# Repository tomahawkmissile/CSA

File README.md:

# CSA

This program was for my final project for my high school computer science class. It is very basic and it is non-modular. It takes in an EAGLE board XML file and is able to produce a couple of metrics about it. These metrics include listing all capacitors, getting the total length of all copper traces of a certain signal, and getting the total area of all copper polygons of a certain signal.

Usage: java -jar XML.jar <file> [args]

Arguments Available:
# demo                =   run demonstration program
# listCapacitors      =   list capacitors in EAGLE XML document
# getLength <signal>  =   get total signal length of a given signal name
# getArea <signal>    =   get total signal polygon area given a signal name

**Note: output may be very large, and you will have the option to save it to a text file.**

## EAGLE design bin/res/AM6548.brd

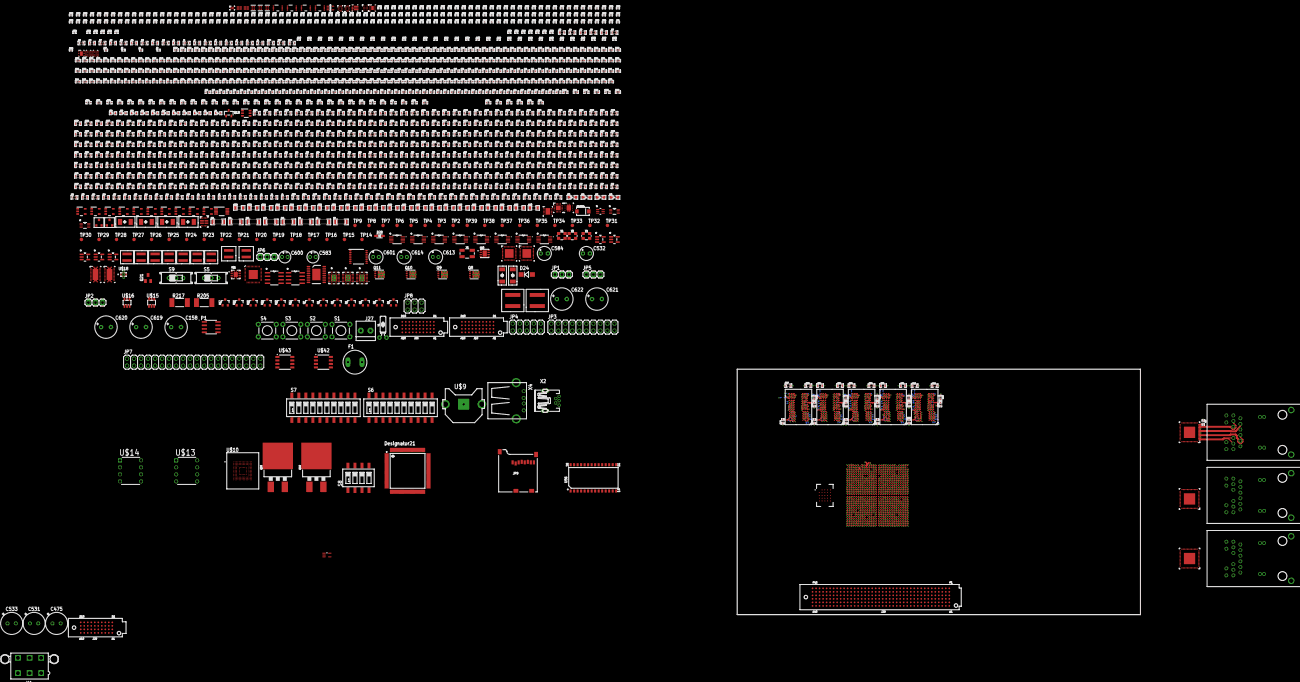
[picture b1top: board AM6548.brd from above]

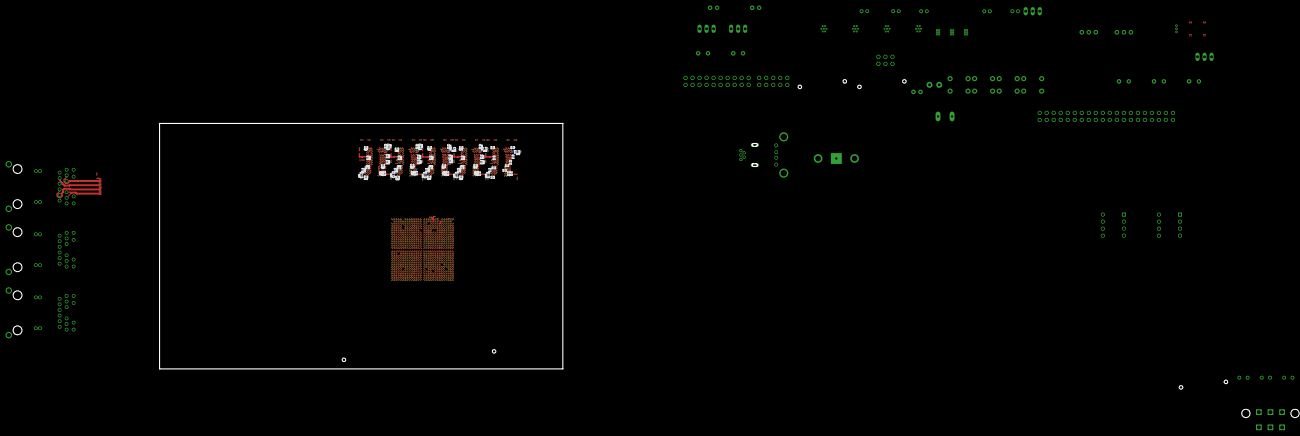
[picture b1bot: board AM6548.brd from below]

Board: 12 copper layers, 1462 parts (66 on the bottom side), 1005 nets.

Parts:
C1, C2, C3, C4, C5, C6, C7, C8, C9, C10, C11, C12, C13, C14, C15, C16, C17, C18, C19, C20, C21, C22, C23, C24, C26, C27, C28, C29, C52, C91, C92, C93, C94, C95, C96, C152, C153, C182, C184, C185, C192, C195, C206, C207, C426, C427, C447, C448, C449, C450, C451, C452, C453, C454, C455, C456, C457, C465, C466, C467, C474, C501, C502, C521, C525, C526, C527, C530, C568, C570, C576, C581, C591, C593, C595, C596: 0.1uF; 0603
C25, C30, C155, C165, C173, C178, C186, C201, C211, C212, C520, C522: 0.01uF; 0603
C31, C47, C166, C168, C204: 2.2uF; 0603
C32, C151, C179, C180, C191, C468, C569, C571, C592, C594, C602, C603: 1uF; 0603
C33: 15pF; 0603
C34, C78, C87, C90, C175, C181, C203, C205, C209, C484, C491, C496, C507, C514, C519, C529: 10uF; 0603
C35, C40, C41, C42, C43, C65, C66, C67, C69, C341, C343, C344, C358, C360, C361, C375, C377, C378, C392, C394, C395, C409, C411, C412, C523, C524, C575: 0.01uF; 0402
C36, C38, C39, C45, C48, C51, C53, C54, C55, C56, C57, C58, C59, C60, C61, C62, C63, C64, C70, C71, C72, C73, C79, C80, C81, C82, C85, C98, C342, C359, C376, C393, C410, C476, C477, C478, C479, C485, C486, C487, C492, C493, C497, C498, C499, C500, C508, C509, C510, C515, C516, C572, C574, C578, C579, C587, C588, C589, C590, C597: 0.1uF; 0402
C37, C44, C46, C74, C75, C76, C77, C83, C84, C86, C88, C89, C480, C481, C482, C483, C488, C489, C490, C494, C495, C503, C504, C505, C506, C511, C512, C513, C517, C518, C609, C632, C633: 1uF; 0402
C49, C50: 18pF; 0603
C68, C97: 8.2pF; 0402
C99, C111, C112, C113, C114, C115: 2.2uF; 0201
C100, C101, C102, C103, C104, C105, C106, C107, C108, C109, C110, C118, C119, C120, C121, C132, C133, C134, C135, C146, C147, C160, C218, C226, C227, C233, C234, C243, C244, C252, C253, C254, C255, C269, C289, C290, C303, C340: 1uF; 0201
C116, C117, C130, C131, C144, C145, C231, C232, C241, C242, C250, C251: 10uF; 0201
C122, C123, C124, C125, C126, C127, C128, C129, C136, C137, C138, C139, C140, C141, C142, C143, C219, C220, C221, C222, C223, C224, C225, C228, C229, C230, C235, C236, C237, C238, C239, C240, C245, C246, C247, C248, C249, C256, C257, C258, C259, C260, C261, C262, C263, C264, C265, C266, C267, C268, C270, C271, C272, C273, C274, C275, C276, C277, C278, C279, C280, C281, C282, C283, C284, C285, C286, C287, C288, C291, C293, C294, C295, C296, C297, C298, C299, C300, C304, C305, C307, C308, C309, C310, C311, C312, C313, C314, C315, C316, C317, C319, C320, C321, C322, C323, C324, C325, C326, C327, C328, C329, C330, C332, C334, C335, C336, C337, C338, C339, C430, C431, C432, C433, C434, C435, C436, C437, C438, C439, C440, C441, C442, C443, C444, C445: 0.1uF; 0201
C148, C149, C464, C469, C470, C472, C528: 4.7uF; 0603
C150: 0.47uF; 0805
C154, C172, C606: 100pF; 0603
C156, C171: 0.056uF; 0603
C157, C161, C174, C187, C188, C189, C190, C615, C616: 47uF; 0805
C158: 220uF; E3,5-8
C159: 100uF; 0805
C162, C193, C586: 10uF; 0805
C163: 1uF; 0805
C164, C194, C582: 0.1uF; 0805
C167, C608, C617, C618: 0.47uF; 0603
C169, C170: 33pF; 0603
C176, C177, C183, C198, C199, C446, C611, C623: 22uF; 0603
C196: 0.015uF; 0603
C197: 150pF; 0603
C200: 200pF; 0603
C202, C210, C213, C214, C345, C350, C362, C367, C379, C384, C396, C401, C413, C418: 22uF_6.3V; 0603
C208, C471, C473: 0.22uF; 0603
C215, C216, C217, C580: DNI; 0603
C292, C301, C302, C306, C318, C331, C333, C346, C347, C348, C349, C351, C352, C353, C354, C355, C356, C357, C363, C364, C365, C366, C368, C369, C370, C371, C372, C373, C374, C380, C381, C382, C383, C385, C386, C387, C388, C389, C390, C391, C397, C398, C399, C400, C402, C403, C404, C405, C406, C407, C408, C414, C415, C416, C417, C419, C420, C421, C422, C423, C424, C425, C428, C429, C610, C628, C629, C630, C631: 0.01uF; 0201
C458, C459: 12.5pF; 0402
C460, C461, C462, C463, C566, C567: TBD; 0402
C475, C531: 470uF; CAPPRD300W65D800H1200B
C532: 100uF_10V; E2,5-5
C533: 680uF; CAPPRD300W65D800H1200B
C577: DNI; 0402
C583: 22uF_100V; E2-4
C584: 100uF_63V; E2,5-5
C585: 22uF; 0805
C598: 4.7uF; 0402
C599, C624, C625, C626: 1000pF; 0603
C600: 2.2uF; E2-4
C601: 10uF; E2-5
C604: 0.047uF; 0603
C605: 220pF; 0603
C607: 820pF; 0603
C612, C627: DNI; 0201
C613: 100uF; E2-5
C614: 220uF; E2-5
C619, C622: 270uF; E3,5-8
C620, C621: 470uF; E3,5-8
C634, C635: 22uF; 0402
D1: Blue; 0603.LED
D2: Purple; 0603.LED
D3, D4, D7, D23: TPD1E10B06DPYT; DFN100X60X45-2N
D5, D6: Green; 0603.LED
D8, D19, D20, D21, D22, D31: White; 0603.LED
D24: SUM60N10; DO214BA
D25: Orange; 0603.LED
D26, D29: Red; 0805.LED
D27: Blue; 0805.LED
D28: BZT52C13S; SOD-323
D30: Green; 0805.LED
F1: 10A; TR5
FL1, FL2, FL4, FL5, FL6, FL7, FL8, FL9, FL10, FL11, FL12, FL13, FL14, FL15, FL16, FL17, FL18, FL19: 120R; 0402
FL3: 240R; 0402
FL20, FL21: 26R; 0402
FL22: 120R; 0603
FL26, FL27, FL28: 0603
FL50: DNI; 0402
FL51: 120E; 0402
J1, J2, J3, J4, J5, J6, J7, J8, J9, J11, J12, J13, J14, J15, J16, J17, J18, J19, J20, J21, J22, J23, J24, J25: 0603
J10, J26, J29: SEAF-10-XX.X-XX-04-X-A
J27: 1X2-3.5MM
J28: SEAF-40-XX.X-XX-06-X-A
JP1: PORZ_BYP; 1X03
JP2, JP5: I2C_COMBINE; 1X03
JP3: JTAG-20-ARM; 2X10
JP4: JTAG-10-TM4C; 2X05
JP6: 1X03
JP7: AUTOMATOR; 2X20
JP8: 2X03
JP9: USD-SDIO-SOCKET; MICRO-SD-SOCKET-SDIO
P1: SOIC127P600X175-8N
Q1, Q2, Q3, Q4, Q5, Q6, Q7, Q12, Q13, Q14, Q15, Q16, Q17: 220mA/50V/3.5Ω; SOT23-3
Q8, Q9, Q10, Q11: CSD18543Q3A; SON65P300X315X90-9N
Q18: SOT23-R
Q19, Q20: 100A/100V/6.8mΩ; TO-263/D2PAK
Q21: BSS138; SOT23
R1, R2, R4, R5, R7, R8, R10, R11, R13, R14, R16, R17, R19, R20, R22, R23: 10_1%; 0603
R3, R9, R12: 0.002_1%; 1206
R6, R15, R18, R21, R24: 0.01_0.5%; 1206
R25, R26, R28, R29, R30, R31, R32, R33, R34, R35, R36, R37, R38, R39, R40, R123, R124, R125, R126, R152, R208, R230, R237, R243, R256, R257, R258, R551, R553, R617: 100k; 0603
R27, R328, R342: 11k_1%; 0402
R41: 2.2k; 0603
R42, R43, R44, R45, R46, R47, R48, R49, R50, R51, R52, R53, R330, R331, R332, R333, R334, R335, R336, R337, R338, R339, R340, R341, R344, R345, R346, R347, R348, R352, R358, R359, R360, R361, R362, R363: 22_1%; 0402
R54, R55, R58, R63, R64, R70, R89, R102, R103, R223, R225, R226, R229, R252, R262, R263, R264, R282, R287, R288, R289, R290, R291, R292, R293, R294, R295, R296, R297, R310, R324, R325, R326, R327, R351, R364, R377, R385, R402, R403, R404, R405, R418, R461, R462, R497, R529, R532, R533, R534, R535, R539, R559, R575, R576, R578, R579, R594, R613, R614, R615, R616: 10k; 0603
R56, R57, R59, R60, R61, R62, R90, R178, R179, R241, R242, R265, R283, R284, R311, R349, R350, R365, R366, R372, R373, R374, R375, R376, R378, R379, R380, R381, R382, R383, R384, R484: DNI; 0603
R65, R66, R67, R96, R101, R206, R224, R353, R354, R355, R367, R368, R369, R524, R525, R527, R530, R550: 0R; 0603
R68, R69, R78, R219, R356, R357, R526, R528, R531: 220R; 0603
R71: 51k; 0603
R72, R93, R97, R107, R117, R149, R281, R300, R323, R388, R389, R393, R417, R494, R496, R582, R584, R585, R586, R587, R588, R589, R590, R591: 10k; 0402
R73, R98, R312, R313, R314, R315, R316, R317, R318, R319, R320, R321, R322, R501, R502, R503, R504, R505, R506, R507, R560, R561, R562, R563, R580: 22R_1%; 0402
R74, R91: 100R; 0603
R75: 330k_1%; 0603
R76: 220k_1%; 0603
R77: 180R; 0603
R79, R80, R81, R82, R170, R171, R172, R173, R174, R175, R176, R201, R244, R245, R246, R247, R248, R249, R250, R251, R253, R254, R255, R511, R512: 1k; 0402
R83, R84, R85, R86, R94, R134, R135, R136, R137, R138, R139, R140, R303, R304, R307, R386, R387, R390, R391, R392, R394, R395, R396, R397, R398, R399, R419, R420, R421, R422, R423, R424, R425, R426, R427, R428, R429, R430, R431, R432, R433, R434, R435, R436, R437, R438, R439, R440, R441, R442, R443, R444, R445, R446, R447, R448, R449, R450, R451, R452, R453, R454, R455, R456, R457, R458, R459, R460, R493, R495, R498, R508, R568, R569, R570, R571, R572, R596: DNI; 0402
R87, R99, R100, R106, R485, R486, R487, R488: 4.7k; 0402
R88: 4.87k_1%; 0402
R92: 51R; 0402
R95, R114, R177, R285, R286, R489, R490, R491, R492, R556, R592, R593: 4.7k; 0603
R104, R105, R115, R116, R133: 33R_1%; 0402
R108, R110, R111, R112, R113: 10R_1%; 0603
R109, R118, R509, R510: 100R; 0402
R119, R120, R121, R122, R153, R154, R155, R156, R157, R158, R159, R160, R161, R162, R163, R165, R166, R167, R168, R169, R259, R260, R261, R607, R618: 1k; 0603
R127, R128, R129, R130, R131, R132, R583: 100k; 0402
R141, R238: 40.2k_1%; 0603
R142, R234, R554, R601: 10k_1%; 0603
R143, R299, R301, R302, R305, R306, R308, R309, R499, R500, R543, R573, R577: 0R; 0402
R144, R145, R146, R147, R148, R150: 240R_1%; 0402
R151, R412, R413, R414, R415, R416: 330R; 0402
R164, R180, R181, R182, R184: DNI; 0201
R183: 10k; 0201
R185: 1K; 0201
R186, R187, R188, R189, R190, R191, R192, R193, R194, R195, R196, R197, R198, R199, R200, R209, R210, R266, R267, R268, R269, R270, R271, R272, R273, R274, R275, R276, R277, R278, R279, R280: 39.2R_1%; 0201
R202, R203, R204, R211, R212, R213: 10.2R; 0603
R205, R217: 0.005R; R2512
R207: 19.6k 0.1%; 0603
R214, R215, R216: 49.9R; 0603
R218: 29.4k 1%; 0603
R220: 330R; 0603
R221: 10.2k_0.1%; 0603
R222: 20.5k; 0603
R227: 60.4k; 0603
R228: 40.2k; 0603
R231: 2.05k_1%; 0603
R232: 51.1_1%; 0603
R233: 31.6k_1%; 0603
R235: 18.7_1%; 0603
R236: 8.87_1%; 0603
R239: 158k_1%; 0603
R240: 499k_1%; 0603
R298, R608, R609: 330; 0603
R329, R343, R463, R464: 2.2k; 0402
R370, R371: 220; 0603
R400, R401, R599: 22R; 0603
R406, R409: 16k_1%; 0603
R407, R410: 76.8k_1%; 0603
R408, R411: 23.2k_1%; 0603
R536: 261k_1%; 0402
R537, R538, R541, R542: 10k_1%; 0402
R540: 5.81k_1%; 0402
R544: 237k_1%; 0603
R545, R546: 47k_1%; 0603
R547: 666k_1%; 0603
R548: 5.62k_1%; 0603
R549, R555: 10k; 0805
R552: 1k; 0805
R557, R558: 3k_1%; 0402
R564, R565, R566, R567: 49.9R_1%; 0402
R574, R610, R611, R612: 1M; 0603
R581: 10R_1%; 0402
R595, R597, R598: 22R; 0402
R600: 75k_1%; 0603
R602: 18.2k_1%; 0603
R603: 0.082R_2%; 0603
R604: 1k_1%; 0603
R605: 8.66k_1%; 0603
R606: 46.4k_1%; 0603
R700, R701: 2.2k; 0201
S1, S2, S3, S4: TACTILE-PTH
S5, S9: EG1218
S6, S7: BOOTMODE; SMS-010
S8: MCU_BOOTMODE; SMS-004
SMCJ64CA: TVS; SMA-DIODE
TP2, TP3, TP4, TP5, TP6, TP7, TP8, TP9, TP14, TP15, TP16, TP17, TP18, TP19, TP20, TP21, TP22, TP23, TP24, TP25, TP26, TP27, TP28, TP29, TP30, TP31, TP32, TP33, TP34, TP35, TP36, TP37, TP38, TP39: TESTPAD_TPSQB1,27; TESTPAD_B1,27
U1: Value; ACD0784A
U2, U3, U4, U5, U6, U7, U8, U9: INA226_DGS_10; DGS10
U10: Value; RGJ0032A
U11, U12: Value; RHL0024A
U13, U21, U25: SN74AVC4T245_RGY_16; RGY16_2P55X2P05
U14, U54, U55: Value; RGZ0048B
U15, U75: Value; RSW0010A
U16, U24, U27, U46: Value; DCU0008A_N
U17, U33, U49, U50, U51, U52, U57, U58, U81, U82: Value; DBV0005A_N
U18: Value; PDT0128A_N
U19: TPD4E004_DRY_6; DRY6
U20: Value; DCK0005A_N
U22, U26: SN74AVC2T244_DQM_8; DQM8
U23, U28, U29, U30, U31: SN74LVC1G32_DBV_5; DBV5
U32: Value; PW0016A_N
U34: Value; RWG0040A
U35: Value; RLT0007A
U36, U42: Value; RWK0011B
U37: Value; DQN0004A
U38: Value; YZH0016AFAF
U39: Value; RNC0016A
U40: Value; DRV0006A
U41: Value; DRC0010J
U43: Value; DRB0008A
U44: Value; DSQ0010A
U45: Value; RGT0016C
U47, U48: SN74LVC3G17_DCU_8; DCU8
U53, U59: TPS2051B_D_8; D8
U56: INTERFACE-MCP23017-E(SOIC28); SOIC28-1.27-17.9X7.5MM
U60: TPD4S012_DRY_6; DRY6
U73: Value; RHB0032D
U76: Value; DDC0006A_N
U77: TPS3897_DRY_6; DRY6
U78: SN74LVC1G11_DCK_6; DCK6
U79: Value; DGS0010A_N
U80: MIC5060YML-TR; SON65P300X300X100-9N
U83: Value; PWP0020A_N
U$1: VSON8; SON65P300X300X100-9N
U$2: LM4040B25IDCKR13; SOT65P210X110-5N
U$3, U$4, U$5, U$6, U$7: MT40A1G8WE-083E:B
U$9: CR1220-THM
U$10: IS21ES16G; BGA153C50P14X14_1150X1300X100N
U$11, U$12, U$17: JK0-2500NL
U$13, U$14: 24LC512-E/P; DIP254P762X432-8
U$15, U$16: TMP100; SOT23-6
U$18: NFM21PC; FIL_NFM21PC105B1C3D
U$19, U$36: BZX84C2V4LT1-D; SOT-23
U$20, U$21: DB2441700L
U$22, U$25: XEL6030-152MEB
U$28, U$30, U$31, U$32: XFL4015-471MEB
U$29, U$34, U$35: XFL4020-102MEB
U$33: XEL4030-682ME_
U$38: MT35XU512ABA1G12-0SITT-PBGA-24; BGA25C100P5X5_800X600X100
U$39: XAL40XX
U$40, U$41, U$44, U$45: SSB44-E3/52T; SMB
U$42, U$43: SI4442DYSO-8; SOIC127P600X175-8
X1: 5566-6
X2: MINI-USB_SHIELD5P2-32005-601; 32005-601
X4: USB-A-H
Y1: 32.768kHz; CRYSTAL-PTH-2X6-CYL
Y2: 16MHz; CRYSTAL-SMD-5X3.2-4PAD
Y3, Y6: 25MHz; CRYSTAL-SMD-3.2X2.5MM
Y4: 24.576MHz; CRYSTAL-SMD-3.2X2.5MM

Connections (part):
!APP_RESET: J28.E1, R461.1, U33.4
!BOOTMODE_DEBUGGER_RST: JP7.21, R287.1, U10.28, U56.2
!BOOTMODE_EN: JP7.19, R262.1, R288.1, U23.1, U56.1
!DDR_RESET: R164.1, R180.2, R701.1, U1.A11, U$3.RESET_N, U$4.RESET_N, U$5.RESET_N, U$6.RESET_N, U$7.RESET_N
!EMMC_RST: R364.2, U52.4, U$10.K5
!GPIO_EMMC_RST: R326.1, U52.1, U56.21
!GPIO_MCU_RGMII_RST: R62.2, R63.1, U17.1, U56.23
!GPIO_PRG2_RGMII_RST: R350.2, R351.1, U56.22, U57.1
!JTAG_EMU_RST: JP3.15, R95.1, R111.1, U78.6
!JTAG_TRST: JP3.2, R112.1, U21.10
!LCD_BRD_TOUCH_RESET: R575.1, U56.4, U81.1
!LCD_TOUCH_RESET: J26.B9, R576.1, U81.4
!OSPI_RESET: R578.1, U82.4, U$38.A4
!OSPI_RESET_PRE: R579.1, U56.5, U82.1
!RAW_WARM_RESET: C451.2, D3.1, R295.1, S1.1, S1.2, U48.3
!RAW_WK_INT_0-13: C453.2, D4.1, R296.1, S2.1, S2.2, U48.2
!RAW_WK_INT_0-27: C454.2, D7.1, R297.1, S3.1, S3.2, U48.1
!REG_WK_INT_0-13: U48.6, U50.2
!REG_WK_INT_0-27: U48.7, U51.2
!SOC_TRST: R106.1, U1.AA3, U21.7, U25.7
!SOC_WARM_RESET: U1.F17, U49.4
!SOC_WK_INT_0-13: U1.R5, U50.4
!SOC_WK_INT_0-27: U1.P2, U51.4
!SUPERVISOR_MASTER_RESET: U47.7, U77.1
!SUPERVISOR_RAW_RESET: C576.2, D23.1, Q18.3, R539.1, S4.1, S4.2, U47.1
!TEST_LED: D8.P$2, JP7.13, R291.1
!TEST_PORZ: JP7.9, Q18.2, R293.1
!TEST_WARM_RESET: JP7.11, R292.1, U49.2
!TEST_WK_INT_0-13: JP7.15, R290.1, U50.1
!TEST_WK_INT_0-27: JP7.17, R289.1, U51.1
!TM4C_RST: JP4.10, R91.1
!WARM_RESET: U48.5, U49.1
!XDS_TRST: U18.40, U25.10
ADDR: R263.2, U10.26
BOARDID_EEPROM_A0: R373.1, R374.2, U$13.1
BOARDID_EEPROM_A1: R372.1, R375.2, U$13.2
BOARDID_EEPROM_A2: R366.1, R376.2, U$13.3
BOARDID_EEPROM_WP: R365.1, R377.2, U$13.7
BOARDID_LCD_A1: J26.B4, R577.1
BOOST_DRIVE: U83.15, U$43.4
BOOTMODE_I2C_SCL: JP7.29, R285.1, U10.29
BOOTMODE_I2C_SDA: JP7.27, R286.1, U10.30
BOOTMODE_ON: U11.22, U12.22, U13.14, U13.15, U23.4
BOOT_EEPROM_A0: R381.1, R382.2, U$14.1
BOOT_EEPROM_A1: R380.1, R383.2, U$14.2
BOOT_EEPROM_A2: R379.1, R384.2, U$14.3
BOOT_EEPROM_WP: R378.1, R385.2, U$14.7
BUCK_DRIVE: U83.19, U$42.4
CAP_VDDA_1P8_IOLDO0: C113.2, U1.AA10, U1.AA16, U1.G12, U1.G19, U1.P20
CAP_VDDA_1P8_IOLDO_WKUP: C114.2, U1.AA8, U1.V8
CAP_VDDA_1P8_SDIO: C111.2, U1.G17, U1.J17, U1.K20
CAP_VDDSHV_SDLDO: C99.2, FL20.1, U1.H18
CAP_VDD_WKUP: C115.2, C326.2, C327.2, C328.2, C329.2, U1.M22, U1.V9, U1.V11, U1.W10, U1.W12
CS: R603.1, U83.12, U$44.ANODE, U$45.ANODE
CSI0_RX0_N: J28.A3, U1.G28
CSI0_RX0_P: J28.A2, U1.F28
CSI0_RX1_N: J28.A6, U1.H27
CSI0_RX1_P: J28.A5, U1.G27
CSI0_RX2_N: J28.A8, U1.F26
CSI0_RX2_P: J28.A9, U1.G26
CSI0_RX3_N: J28.A12, U1.H25
CSI0_RX3_P: J28.A11, U1.G25
CSI0_RX4_N: J28.A15, U1.G24
CSI0_RX4_P: J28.A14, U1.F24
DDR_A0: R196.1, U1.A10, U$3.A0, U$4.A0, U$5.A0, U$6.A0, U$7.A0
DDR_A1: R197.1, U1.D9, U$3.A1, U$4.A1, U$5.A1, U$6.A1, U$7.A1
DDR_A2: R198.1, U1.C9, U$3.A2, U$4.A2, U$5.A2, U$6.A2, U$7.A2
DDR_A3: R199.1, U1.E9, U$3.A3, U$4.A3, U$5.A3, U$6.A3, U$7.A3
DDR_A4: R200.1, U1.A9, U$3.A4, U$4.A4, U$5.A4, U$6.A4, U$7.A4
DDR_A5: R209.1, U1.E8, U$3.A5, U$4.A5, U$5.A5, U$6.A5, U$7.A5
DDR_A6: R210.1, U1.F8, U$3.A6, U$4.A6, U$5.A6, U$6.A6, U$7.A6
DDR_A7: R266.1, U1.C7, U$3.A7, U$4.A7, U$5.A7, U$6.A7, U$7.A7
DDR_A8: R267.1, U1.C8, U$3.A8, U$4.A8, U$5.A8, U$6.A8, U$7.A8
DDR_A9: R268.1, U1.D7, U$3.A9, U$4.A9, U$5.A9, U$6.A9, U$7.A9
DDR_A10: R269.1, U1.E7, U$3.A10/AP, U$4.A10/AP, U$5.A10/AP, U$6.A10/AP, U$7.A10/AP
DDR_A11: R270.1, U1.A6, U$3.A11, U$4.A11, U$5.A11, U$6.A11, U$7.A11
DDR_A12: R271.1, U1.F7, U$3.A12/BC_N, U$4.A12/BC_N, U$5.A12/BC_N, U$6.A12/BC_N, U$7.A12/BC_N
DDR_A13: R272.1, U1.D6, U$3.A13, U$4.A13, U$5.A13, U$6.A13, U$7.A13
DDR_A14_WEN: R273.1, U1.C6, U$3.WE_N/A14, U$4.WE_N/A14, U$5.WE_N/A14, U$6.WE_N/A14, U$7.WE_N/A14
DDR_A15_CAS: R274.1, U1.F6, U$3.CAS_N/A15, U$4.CAS_N/A15, U$5.CAS_N/A15, U$6.CAS_N/A15, U$7.CAS_N/A15
DDR_A16_RAS: R275.1, U1.E6, U$3.RAS_N/A16, U$4.RAS_N/A16, U$5.RAS_N/A16, U$6.RAS_N/A16, U$7.RAS_N/A16
DDR_A17: R276.1, U1.E5, U$3.A17/NC, U$4.A17/NC, U$5.A17/NC, U$6.A17/NC, U$7.A17/NC
DDR_ACT_N: R280.1, U1.D8, U$3.ACT_N, U$4.ACT_N, U$5.ACT_N, U$6.ACT_N, U$7.ACT_N
DDR_ALERT_N: R183.1, U1.D5, U$3.ALERT_N, U$4.ALERT_N, U$5.ALERT_N, U$6.ALERT_N, U$7.ALERT_N
DDR_BA0: R194.1, U1.D10, U$3.BA0, U$4.BA0, U$5.BA0, U$6.BA0, U$7.BA0
DDR_BA1: R195.1, U1.E10, U$3.BA1, U$4.BA1, U$5.BA1, U$6.BA1, U$7.BA1
DDR_BG0: R278.1, U1.C10, U$3.BG0, U$4.BG0, U$5.BG0, U$6.BG0, U$7.BG0
DDR_BG1: R279.1, U1.F11, U$3.BG1, U$4.BG1, U$5.BG1, U$6.BG1, U$7.BG1
DDR_CKE: R182.2, R190.1, U1.C11, U$3.CKE, U$4.CKE, U$5.CKE, U$6.CKE, U$7.CKE
DDR_CKE1: R181.2, R191.1, U1.D12, U$3.C0/CKE1, U$4.C0/CKE1, U$5.C0/CKE1, U$6.C0/CKE1, U$7.C0/CKE1
DDR_CK_N: R187.1, U1.B8, U$3.CK_C, U$4.CK_C, U$5.CK_C, U$6.CK_C, U$7.CK_C
DDR_CK_P: R186.1, U1.A8, U$3.CK_T, U$4.CK_T, U$5.CK_T, U$6.CK_T, U$7.CK_T
DDR_CS1_N: R193.1, U1.E11, U$3.C1/CS1_N, U$4.C1/CS1_N, U$5.C1/CS1_N, U$6.C1/CS1_N, U$7.C1/CS1_N
DDR_CS_N: R192.1, U1.D11, U$3.CS_N, U$4.CS_N, U$5.CS_N, U$6.CS_N, U$7.CS_N
DDR_DM0: U1.E1, U$3.NF/DM_N/DBI_N/TDQS_I
DDR_DM1: U1.C5, U$4.NF/DM_N/DBI_N/TDQS_I
DDR_DM2: U1.D14, U$5.NF/DM_N/DBI_N/TDQS_I
DDR_DM3: U1.B17, U$6.NF/DM_N/DBI_N/TDQS_I
DDR_DM4: U1.C17, U$7.NF/DM_N/DBI_N/TDQS_I
DDR_DQ0: U1.A3, U$3.DQ6/NF
DDR_DQ1: U1.B2, U$3.DQ4/NF
DDR_DQ2: U1.C2, U$3.DQ2
DDR_DQ3: U1.D2, U$3.DQ0
DDR_DQ4: U1.E2, U$3.DQ1
DDR_DQ5: U1.G1, U$3.DQ7/NF
DDR_DQ6: U1.F2, U$3.DQ5/NF
DDR_DQ7: U1.F1, U$3.DQ3
DDR_DQ8: U1.E3, U$4.DQ6/NF
DDR_DQ9: U1.C3, U$4.DQ3
DDR_DQ10: U1.D3, U$4.DQ5/NF
DDR_DQ11: U1.B3, U$4.DQ1
DDR_DQ12: U1.D4, U$4.DQ7/NF
DDR_DQ13: U1.C4, U$4.DQ2
DDR_DQ14: U1.B4, U$4.DQ4/NF
DDR_DQ15: U1.B5, U$4.DQ0
DDR_DQ16: U1.E13, U$5.DQ1
DDR_DQ17: U1.C14, U$5.DQ6/NF
DDR_DQ18: U1.B14, U$5.DQ4/NF
DDR_DQ19: U1.A14, U$5.DQ2
DDR_DQ20: U1.E14, U$5.DQ3
DDR_DQ21: U1.B13, U$5.DQ0
DDR_DQ22: U1.C13, U$5.DQ7/NF
DDR_DQ23: U1.D13, U$5.DQ5/NF
DDR_DQ24: U1.D15, U$6.DQ3
DDR_DQ25: U1.C15, U$6.DQ5/NF
DDR_DQ26: U1.E16, U$6.DQ6/NF
DDR_DQ27: U1.E15, U$6.DQ7/NF
DDR_DQ28: U1.D16, U$6.DQ4/NF
DDR_DQ29: U1.B16, U$6.DQ1
DDR_DQ30: U1.C16, U$6.DQ0
DDR_DQ31: U1.A17, U$6.DQ2
DDR_DQ36: U1.B19, U$7.DQ0
DDR_DQ37: U1.B18, U$7.DQ1
DDR_DQ38: U1.C18, U$7.DQ2
DDR_DQ39: U1.D18, U$7.DQ4/NF
DDR_DQ40: U1.E18, U$7.DQ5/NF
DDR_DQ41: U1.E17, U$7.DQ6/NF
DDR_DQ42: U1.D17, U$7.DQ3
DDR_DQS0_N: U1.C1, U$3.DQS_C
DDR_DQS0_P: U1.D1, U$3.DQS_I
DDR_DQS1_N: U1.A4, U$4.DQS_C
DDR_DQS1_P: U1.A5, U$4.DQS_I
DDR_DQS2_N: U1.A12, U$5.DQS_C
DDR_DQS2_P: U1.A13, U$5.DQS_I
DDR_DQS3_N: U1.A16, U$6.DQS_C
DDR_DQS3_P: U1.A15, U$6.DQS_I
DDR_DQS_N: U1.A18, U$7.DQS_C
DDR_DQS_P: U1.A19, U$7.DQS_I
DDR_ODT: R188.1, U1.B11, U$3.ODT, U$4.ODT, U$5.ODT, U$6.ODT, U$7.ODT
DDR_ODT1: R189.1, U1.E12, U$3.C2/ODT1, U$4.C2/ODT1, U$5.C2/ODT1, U$6.C2/ODT1, U$7.C2/ODT1
DDR_PARITY: R277.1, U1.B10, U$3.PAR, U$4.PAR, U$5.PAR, U$6.PAR, U$7.PAR
DDR_TEN: R184.1, R185.2, U$3.TEN, U$4.TEN, U$5.TEN, U$6.TEN, U$7.TEN
DDR_VPP: C343.2, C344.2, C345.2, C360.2, C361.2, C362.2, C377.2, C378.2, C379.2, C394.2, C395.2, C396.2, C411.2, C412.2, C413.2, FL51.2, U$3.VPP@1, U$3.VPP@2, U$4.VPP@1, U$4.VPP@2, U$5.VPP@1, U$5.VPP@2, U$6.VPP@1, U$6.VPP@2, U$7.VPP@1, U$7.VPP@2
DDR_VREFCA: C208.2, C341.2, C342.2, C358.2, C359.2, C375.2, C376.2, C392.2, C393.2, C409.2, C410.2, R179.1, U44.6, U$3.VREFCA, U$4.VREFCA, U$5.VREFCA, U$6.VREFCA, U$7.VREFCA
DDR_VTT_EN: U1.P3, U75.4
DDR_VTT_EN_3V3: R237.2, U44.7, U44.9, U75.9
DIR: R264.2, R265.1, U11.2, U12.2, U13.2, U13.3
DOCK_TCK: R115.2, U32.2
ECAP0_IN_APWM0_OUT: J26.B8, U1.D21
GPIO0_16: J28.B4, U1.R28
GPIO0_20: J28.B6, U1.T28
GPIO0_21: J28.A39, R462.1, U1.P23, U33.1
GPIO0_22: J28.B9, U1.R26
GPIO0_23: J28.B7, U1.R23
GPIO0_25: J28.B8, U1.T24
GPIO0_26: J28.B5, U1.R24
GPIO0_27: J28.A38, U1.T23
GPIO1_0: J28.B10, R609.1, U1.AD18
GPIO1_1: J28.B11, R608.1, U1.AH18
GPIO1_69: J28.B12, U1.AE26
GPIO1_70: J28.B13, U1.AE28
GPIO_0-0-0: J28.D20, U1.V24
GPIO_0-0-1: J28.F28, U1.W25
GPIO_0-0-2: J28.D23, U1.W24
GPIO_0-0-3: J28.D28, U1.AA27
GPIO_0-0-4: J28.D25, U1.Y24
GPIO_0-0-5: J28.D17, U1.V28
GPIO_0-0-6: J28.D26, U1.Y25
GPIO_0-0-7: J28.D18, U1.U27
GPIO_0-0-8: J28.D19, U1.V27
GPIO_0-0-11: J28.D29, U1.AB25
GPIO_0-0-12: J28.D14, U1.AD27
GPIO_0-0-13: J28.D16, U1.AC26
GPIO_0-0-14: J28.D13, U1.AD26
GPIO_0-0-15: J28.D27, U1.AA24
GPIO_0-0-16: J28.D15, U1.AD28
GPIO_0-0-17: J28.D21, U1.U26
GPIO_0-0-18: J28.D24, U1.V25
GPIO_0-0-19: J28.D22, U1.U24
GPIO_0-1-0: J28.D40, U1.AB28
GPIO_0-1-1: J28.C39, U1.AC28
GPIO_0-1-2: J28.C37, U1.AC27
GPIO_0-1-3: J28.C38, U1.AB26
GPIO_0-1-4: J28.D37, U1.AA25
GPIO_0-1-5: J28.D38, U1.U23
GPIO_0-1-6: J28.D39, U1.AB27
GPIO_0-1-8: J28.C40, U1.W27
GPIO_0-1-11: J28.D36, U1.AB24
GPIO_0-1-12: J28.D35, U1.AC25
GPIO_0-1-13: J28.D32, U1.AD25
GPIO_0-1-14: J28.D33, U1.AD24
GPIO_0-1-15: J28.D31, U1.AE27
GPIO_0-1-16: J28.D34, U1.AC24
GPIO_1-0-0: J28.D12, U1.AE22
GPIO_1-0-1: J28.D6, U1.AG24
GPIO_1-0-2: J28.E7, U1.AF23
GPIO_1-0-3: J28.E13, U1.AD21
GPIO_1-0-4: J28.D7, U1.AG23
GPIO_1-0-5: J28.D2, U1.AF27
GPIO_1-0-6: J28.D9, U1.AF22
GPIO_1-0-7: J28.D3, U1.AG27
GPIO_1-0-8: J28.D1, U1.AF28
GPIO_1-0-11: J28.D11, U1.AF21
GPIO_1-0-12: J28.D10, U1.AH20
GPIO_1-0-13: J28.D8, U1.AH21
GPIO_1-0-14: J28.E10, U1.AG20
GPIO_1-0-15: J28.E16, U1.AD19
GPIO_1-0-16: J28.E19, U1.AD20
GPIO_1-0-17: J28.D4, U1.AH26
GPIO_1-0-18: J28.D5, U1.AG25
GPIO_1-0-19: J28.E4, U1.AG26
GPIO_1-1-0: J28.E26, U1.AH24
GPIO_1-1-1: J28.E36, U1.AH23
GPIO_1-1-2: J28.F29, U1.AG21
GPIO_1-1-3: J28.E29, U1.AH22
GPIO_1-1-4: J28.E28, U1.AE21
GPIO_1-1-5: J28.E27, U1.AC22
GPIO_1-1-6: J28.E35, U1.AG22
GPIO_1-1-8: J28.E25, U1.AE24
GPIO_1-1-11: J28.E34, U1.AC20
GPIO_1-1-12: J28.D30, U1.AE20
GPIO_1-1-13: J28.E30, U1.AF19
GPIO_1-1-14: J28.E31, U1.AH19
GPIO_1-1-15: J28.E32, U1.AG19
GPIO_1-1-16: J28.E33, U1.AE19
GPIO_SGMII_PHY_INT: J28.E22, R101.1, R559.2
HB: C608.1, U83.18
HS: C608.2, U83.20, U$39.P$1, U$42.1, U$42.2, U$42.3, U$44.CATHODE, U$45.CATHODE
HS_L: U$39.P$2, U$40.ANODE, U$41.ANODE, U$43.5, U$43.6, U$43.7, U$43.8
INA_ALERT: R417.1, U2.3, U3.3, U4.3, U5.3, U6.3, U7.3, U8.3, U9.3, U56.26
JTAG_DIR: R72.2, U21.2, U21.3
JTAG_DOCK_EMU0_1V8: J10.C4, R177.1, U46.5
JTAG_DOCK_EMU1_1V8: J10.C5, R114.1, U46.4
JTAG_DOCK_RTCK: J10.A7, R116.2
JTAG_DOCK_TCK: J10.A6, R117.1, R118.2, U30.2, U31.2
JTAG_EMU0: JP3.13, R100.1, U24.8, U46.8
JTAG_EMU1: JP3.14, R99.1, U24.1, U46.1
JTAG_PERIF_RTCK: JP3.9, R105.2
JTAG_PERIF_TCK: JP3.11, R107.1, R109.2, U28.2, U29.2
JTAG_TCK: U21.12, U32.4
JTAG_TDI: JP3.3, R113.1, U21.13
JTAG_TDIS: JP3.4, R96.2
JTAG_TDO: JP3.7, R110.1, U22.7
JTAG_TMS: JP3.1, R108.1, U21.11
LCD_BRD_DET: J26.B10, U56.24
LCD_BRD_TOUCH_INT: J26.C9, U56.6
LCD_DISPLAY_EN: J26.C10, R596.2, U56.3
LM25118_COMP: C606.2, R606.2, U83.9
LM25118_FB: C606.1, C607.1, R604.1, R605.1, U83.8
MAIN: F1.1, J27.1, TP20.TP, X1.3, X1.4
MCAN0_RX: J28.A23, U1.W2
MCAN0_TX: J28.A24, U1.W1
MCP23017_A0: R396.2, R399.1, U56.15
MCP23017_A1: R395.2, R398.1, U56.16
MCP23017_A2: R394.2, R397.1, U56.17
MCP23017_INTA: R401.2, R402.2
MCP23017_INTB: R400.2, R403.2
MCU_ADC0_IN0: J28.F33, U1.K5
MCU_ADC0_IN1: J28.F34, U1.J3
MCU_ADC0_IN2: J28.F35, U1.J1
MCU_ADC0_IN3: J28.F36, U1.J5
MCU_ADC0_IN4: J28.F37, U1.K4
MCU_ADC0_IN5: J28.F38, U1.J4
MCU_ADC0_IN6: J28.F39, U1.J2
MCU_ADC0_IN7: J28.F40, U1.J6
MCU_ADC0_REF_N: C588.2, J28.F32, U1.K2
MCU_ADC0_REF_P: C587.2, J28.F31, U1.K3
MCU_ADC1_REF_N: C589.1, U1.H3
MCU_ADC1_REF_P: C590.1, U1.H2
MCU_BOOTMODE0: R123.1, R525.1, S8.4, U1.AF4
MCU_BOOTMODE1: R124.1, R524.2, S8.3, U1.AF3
MCU_BOOTMODE2: R125.1, S8.2, U1.AE3
MCU_BOOTMODE3: R132.2, R135.1, U1.AD1
MCU_BOOTMODE4: R131.2, R133.2, R136.1, U1.AC3
MCU_BOOTMODE5: R130.2, R137.1, R598.2, U1.Y2
MCU_BOOTMODE6: R129.2, R138.1, R595.2, U1.Y1
MCU_BOOTMODE7: R128.2, R139.1, R597.2, U1.Y3
MCU_BOOTMODE8: R127.2, R140.1, R599.2, U1.AC5
MCU_BOOTMODE9: R126.1, S8.1, U1.AB4
MCU_BYP_PORZ: JP1.2, U1.V5
MCU_CLKOUT: R134.1, R509.1, R510.2, U73.13
MCU_ETH1_D0_N: U14.2, U$17.MD1-
MCU_ETH1_D0_P: U14.1, U$17.MD1+
MCU_ETH1_D1_N: U14.5, U$17.MD2-
MCU_ETH1_D1_P: U14.4, U$17.MD2+
MCU_ETH1_D2_N: U14.8, U$17.MD3-
MCU_ETH1_D2_P: U14.7, U$17.MD3+
MCU_ETH1_D3_N: U14.11, U$17.MD4-
MCU_ETH1_D3_P: U14.10, U$17.MD4+
MCU_ETH1_GPIO0: R67.2, R419.1, R425.2, U14.39
MCU_ETH1_GPIO1: R431.2, R432.1, U14.40
MCU_ETH1_LED1: Q7.3, R413.1
MCU_ETH1_LED2: Q6.3, R68.1, U$17.LED_YG_G+
MCU_ETH1_LED3: Q5.3, R69.1, R414.1
MCU_ETH1_LED_1000: R66.2, R421.1, R427.2, U14.45
MCU_ETH1_LED_ACTIVITY: R65.2, R420.1, R426.2, U14.46
MCU_ETH_INT: R41.1, U14.44
MCU_ETH_RBIAS: R27.2, U14.12
MCU_MCAN1_RX: J28.A21, U1.AD3
MCU_MCAN1_TX: J28.A20, R133.1
MCU_PORZ_OUT: TP2.TP, U1.V2
MCU_RESETSTATZ: TP3.TP, U1.V3
MCU_RESETZ: TP4.TP, U1.W4
MCU_RGMII1_CLKIN: R501.2, U14.15
MCU_RGMII1_MDC_1V8: R56.1, U14.16, U15.8
MCU_RGMII1_MDC_3V3: R57.2, U1.L1, U15.5
MCU_RGMII1_MDIO_1V8: R60.1, U14.17, U16.5
MCU_RGMII1_MDIO_3V3: R59.2, U1.L4, U16.8
MCU_RGMII1_RX0: R45.1, U1.L6
MCU_RGMII1_RX1: R44.1, U1.M6
MCU_RGMII1_RX2: R43.1, U1.L5
MCU_RGMII1_RX3: R42.1, U1.L2
MCU_RGMII1_RXCLK: R46.1, U1.M1
MCU_RGMII1_RXCTL: R47.1, U1.N5
MCU_RGMII1_TX0: R51.1, U1.M5
MCU_RGMII1_TX1: R50.1, U1.M4
MCU_RGMII1_TX2: R49.1, U1.M3
MCU_RGMII1_TX3: R48.1, U1.M2
MCU_RGMII1_TXCLK: R53.1, U1.N1
MCU_RGMII1_TXCTL: R52.1, U1.N4
MCU_RGMII_RESETN: R61.2, U14.43, U17.4
MCU_RGMII_RX0_R: R45.2, R424.1, R430.2, U14.33
MCU_RGMII_RX2_R: R43.2, R423.1, R429.2, U14.35
MCU_RGMII_RXCTL_R: R47.2, R422.1, R428.2, U14.38
MCU_SAFETY_ERRORN: TP5.TP, U1.W3
MCU_SPI0_CLK: J28.E40, R595.1
MCU_SPI0_D0: J28.E38, R597.1
MCU_SPI0_D1: J28.E39, R598.1
MCU_SYSCLKOUT: TP8.TP, U1.AB3
MCU_UART0_CTS: J28.C15, U1.P1
MCU_UART0_RTS: J28.C14, U1.N3
MCU_UART0_RX: J28.C13, U1.P4
MCU_UART0_TX: J28.C12, U1.P5
MMC1_SD_EN: R324.2, U53.4
unnamed: C2.2, R2.1, U2.8, U2.9
unnamed: C2.1, R1.1, U2.10
unnamed: C5.2, R5.1, U3.8, U3.9
unnamed: C5.1, R4.1, U3.10
unnamed: C8.2, R8.1, U4.8, U4.9
unnamed: C8.1, R7.1, U4.10
unnamed: C11.2, R11.1, U5.8, U5.9
unnamed: C11.1, R10.1, U5.10
unnamed: C14.2, R14.1, U6.8, U6.9
unnamed: C14.1, R13.1, U6.10
unnamed: C17.2, R17.1, U7.8, U7.9
unnamed: C17.1, R16.1, U7.10
unnamed: C20.2, R20.1, U8.8, U8.9
unnamed: C20.1, R19.1, U8.10
unnamed: C23.2, R23.1, U9.8, U9.9
unnamed: C23.1, R22.1, U9.10
unnamed: R161.1, S7.20
unnamed: R162.1, S7.19
unnamed: R163.1, S7.18
unnamed: R165.1, S7.17
unnamed: R166.1, S7.16
unnamed: R167.1, S7.15
unnamed: R168.1, S7.14
unnamed: R169.1, S7.13
unnamed: R160.1, S6.13
unnamed: R159.1, S6.14
unnamed: R158.1, S6.15
unnamed: R157.1, S6.16
unnamed: R156.1, S6.17
unnamed: R155.1, S6.18
unnamed: R154.1, S6.19
unnamed: R153.1, S6.20
unnamed: R170.2, U11.21
unnamed: R171.2, U11.20
unnamed: R172.2, U11.19
unnamed: R173.2, U11.18
unnamed: R174.2, U11.17
unnamed: R175.2, U11.16
unnamed: R176.2, U11.15
unnamed: R201.2, U11.14
unnamed: R244.2, U12.21
unnamed: R245.2, U12.20
unnamed: R246.2, U12.19
unnamed: R247.2, U12.18
unnamed: R248.2, U12.17
unnamed: R73.1, U21.5
unnamed: R249.2, U12.16
unnamed: R341.2, U54.29
unnamed: R340.2, U54.37
unnamed: R53.2, U14.29
unnamed: R52.2, U14.37
unnamed: R51.2, U14.28
unnamed: R50.2, U14.27
unnamed: R49.2, U14.26
unnamed: R48.2, U14.25
unnamed: R46.2, U14.32
unnamed: R250.2, U12.15
unnamed: R44.2, U14.34
unnamed: R42.2, U14.36
unnamed: Q7.1, R65.1
unnamed: R58.2, U16.6
unnamed: R55.2, U15.1, U15.10
unnamed: R54.1, U15.2
unnamed: Q6.1, R66.1
unnamed: Q5.1, R67.1
unnamed: D25.P$1, R609.2
unnamed: JP9.CLK, R418.1, U1.C27
unnamed: J4.1, J8.2, U$17.VDC2-
unnamed: R251.2, U12.14
unnamed: R252.2, U13.7
unnamed: R255.1, U13.11
unnamed: R254.1, U13.12
unnamed: R253.1, U13.13
unnamed: R261.1, S6.11
unnamed: R260.1, S6.12
unnamed: R259.1, S7.12
unnamed: R119.2, S8.5
unnamed: R134.2, U1.AB2
unnamed: C33.1, R70.2, R71.1, U$1.NR/FB
unnamed: J3.1, J7.2, U$17.VDC2+
unnamed: C34.2, R74.1, U18.96
unnamed: R75.1, R76.2, U18.1
unnamed: D1.P$1, U18.3
unnamed: D2.P$1, U18.4
unnamed: D1.P$2, R77.1
unnamed: D2.P$2, R78.1
unnamed: R79.1, R86.2, U18.60
unnamed: R80.1, R85.2, U18.61
unnamed: R81.1, R84.2, U18.62
unnamed: R82.1, R83.2, U18.63
unnamed: C35.2, C36.2, R87.1, U18.9, U$2.3
unnamed: R88.1, U18.59
unnamed: C48.2, R92.1, U18.68
unnamed: R98.1, U25.5
unnamed: R89.1, R90.2, R91.2, U18.70
unnamed: JP4.4, U18.100
unnamed: JP4.2, U18.99
unnamed: JP4.6, U18.97
unnamed: JP4.8, U18.98
unnamed: R101.2, U1.F18
unnamed: JP1.1, R103.1
unnamed: JP1.3, R102.2
unnamed: R104.1, U28.4
unnamed: R105.1, U29.4
unnamed: J10.A1, R108.2
unnamed: J10.A2, R110.2
unnamed: J10.A3, R111.2
unnamed: C68.2, R109.1
unnamed: J10.A4, R112.2
unnamed: J10.A9, R113.2
unnamed: J2.1, J6.2, U$17.VDC1-
unnamed: J1.1, J5.2, U$17.VDC1+
unnamed: R115.1, U30.4
unnamed: R116.1, U31.4
unnamed: C97.2, R118.1
unnamed: JP6.2, U32.1
unnamed: R122.2, S8.8
unnamed: R121.2, S8.7
unnamed: R120.2, S8.6
unnamed: R144.2, U$3.ZQ
unnamed: C100.2, U1.Y10
unnamed: C101.2, U1.N15
unnamed: C102.2, U1.N18
unnamed: C103.2, U1.N12
unnamed: C104.2, U1.M12
unnamed: C105.2, U1.U10
unnamed: C106.2, U1.L15
unnamed: C107.2, U1.M14
unnamed: C108.2, U1.W16
unnamed: C109.2, U1.V17
unnamed: C110.2, U1.P17
unnamed: R145.2, U$4.ZQ
unnamed: C112.2, U1.Y19
unnamed: R146.2, U$5.ZQ
unnamed: R147.2, U$6.ZQ
unnamed: R148.2, U$7.ZQ
unnamed: R149.2, U$7.DQ7/NF
unnamed: R150.1, U1.F13
unnamed: R164.2, R700.1, U1.F16
unnamed: R151.2, U$11.LED_G-
unnamed: R178.2, U46.6
unnamed: C430.1, R186.2, R187.2
unnamed: JP9.CD/DAT3, R616.1, U1.D27
unnamed: JP9.DAT2, R615.1, U1.D26
unnamed: JP9.DAT1, R614.1, U1.E27
unnamed: JP9.DAT0, R613.1, U1.D28
unnamed: JP9.CMD, U1.C28
unnamed: JP9.CD1, JP9.CD2, R283.1, R284.2, U1.B24
unnamed: R618.2, S9.P
unnamed: R282.2, U1.D24
unnamed: R281.1, U1.F23
unnamed: D8.P$1, R298.2
unnamed: P1.MFP, R299.1, R300.1
unnamed: C151.2, U34.32
unnamed: P1.X2, R301.2
unnamed: P1.X1, R302.2
unnamed: C152.1, U34.20, U$21.CATHODE
unnamed: C153.2, U34.11, U$20.CATHODE
unnamed: C152.2, Q8.1, Q8.2, Q8.3, Q9.5-9, U34.21, U$22.P$2
unnamed: Q8.4, R202.1, U34.23
unnamed: R202.2, U34.22
unnamed: R618.1, U1.C24
unnamed: Q9.4, R203.1, R204.1
unnamed: R203.2, U34.18
unnamed: R204.2, U34.19
unnamed: R205.2, R214.2, U$22.P$1
unnamed: C169.1, R214.1, U34.27
unnamed: C169.2, R206.1, U34.26
unnamed: C154.2, R207.2, U34.29
unnamed: C155.2, R207.1
unnamed: C156.2, U34.30
unnamed: C153.1, Q10.5-9, Q11.1, Q11.2, Q11.3, U34.10, U$25.P$1
unnamed: Q11.4, R211.1, U34.8
unnamed: R211.2, U34.9
unnamed: R212.1, U34.12
unnamed: R213.1, U34.13
unnamed: Q10.4, R212.2, R213.2
unnamed: R215.2, R217.1, U$25.P$2
unnamed: C170.2, R215.1, U34.4
unnamed: C170.1, R216.1, U34.5
unnamed: C171.2, U34.1
unnamed: C173.1, R218.2
unnamed: C172.1, R218.1, U34.2
unnamed: D6.P$1, R219.2
unnamed: D5.P$1, R220.2
unnamed: U35.6, U$28.P$1
unnamed: C178.1, U36.9
unnamed: U36.2, U$29.V
unnamed: R594.2, U1.V4
unnamed: R221.2, R222.1, U36.4
unnamed: U38.B3, U38.B4, U$30.P$1
unnamed: C186.2, U39.12
unnamed: R224.2, U39.6
unnamed: R225.1, U39.8
unnamed: U39.2, U$31.P$1
unnamed: U39.10, U$32.P$1
unnamed: R227.1, R228.2, R242.1, U39.14
unnamed: C195.2, U41.2, U$33.P$1
unnamed: C195.1, U41.9
unnamed: C196.1, R231.2
unnamed: C197.1, R231.1, U41.7
unnamed: C200.2, R232.1, R233.2
unnamed: C201.2, U42.9
unnamed: U42.2, U$34.V
unnamed: R235.1, R236.2, U42.4
unnamed: C599.2, JP9.GND1, JP9.GND3, R574.2
unnamed: C211.2, U45.7
unnamed: C211.1, U45.8
unnamed: C212.2, U45.9
unnamed: U45.1, U45.2, U$35.V
unnamed: R238.1, R239.2, U45.5
unnamed: R242.2, U39.15
unnamed: C217.2, U43.3
unnamed: C461.2, R304.2, R305.1, Y3.3
unnamed: P1.VBAT, U$9.+1, U$9.+2
unnamed: C459.2, R302.1, R303.2, Y1.2
unnamed: C458.2, R301.1, R303.1, Y1.1
unnamed: C460.2, R304.1, R306.1, Y3.1
unnamed: C463.2, R307.2, R308.1, Y4.3
unnamed: C462.2, R307.1, R309.1, Y4.1
unnamed: R310.2, R311.1, U1.B23
unnamed: C464.1, C465.1, U$10.C2
unnamed: R320.2, R323.1, U1.C25
unnamed: R321.2, U1.B27
unnamed: R322.2, U1.B25
unnamed: R312.2, U1.A26
unnamed: R313.2, U1.E25
unnamed: R314.2, U1.C26
unnamed: R315.2, U1.A25
unnamed: R316.2, U1.E24
unnamed: R317.2, U1.A24
unnamed: R318.2, U1.B26
unnamed: R319.2, U1.D25
unnamed: R312.1, U$10.A3
unnamed: R313.1, U$10.A4
unnamed: R314.1, U$10.A5
unnamed: R315.1, U$10.B2
unnamed: R316.1, U$10.B3
unnamed: R317.1, U$10.B4
unnamed: R318.1, U$10.B5
unnamed: R319.1, U$10.B6
unnamed: R320.1, U$10.H5
unnamed: R321.1, U$10.M5
unnamed: R322.1, U$10.M6
unnamed: R325.1, U53.5
unnamed: R339.2, U54.28
unnamed: R338.2, U54.27
unnamed: R337.2, U54.26
unnamed: R336.2, U54.25
unnamed: R334.2, U54.32
unnamed: R332.2, U54.34
unnamed: R330.2, U54.36
unnamed: R363.2, U55.29
unnamed: R362.2, U55.37
unnamed: R361.2, U55.28
unnamed: Q3.1, R353.1
unnamed: Q2.1, R354.1
unnamed: Q1.1, R355.1
unnamed: J9.1, J17.2, U$11.VDC2-
unnamed: J11.1, J16.2, U$11.VDC2+
unnamed: J12.1, J15.2, U$11.VDC1-
unnamed: J13.1, J14.2, U$11.VDC1+
unnamed: R360.2, U55.27
unnamed: R359.2, U55.26
unnamed: R358.2, U55.25
unnamed: R348.2, U55.32
unnamed: R346.2, U55.34
unnamed: R344.2, U55.36
unnamed: Q13.1, R367.1
unnamed: Q12.1, R368.1
unnamed: Q4.1, R369.1
unnamed: J18.1, J25.2, U$12.VDC2-
unnamed: J19.1, J24.2, U$12.VDC2+
unnamed: J20.1, J23.2, U$12.VDC1-
unnamed: J21.1, J22.2, U$12.VDC1+
unnamed: R386.1, R388.2, U$15.P$5
unnamed: R387.1, R389.2, U$15.P$3
unnamed: R390.1, R392.2, U$16.P$5
unnamed: R391.1, R393.2, U$16.P$3
unnamed: U56.18, U58.4
unnamed: R401.1, U56.19
unnamed: R400.1, U56.20
unnamed: C529.2, U59.2, U59.3, U$18.3
unnamed: R404.1, U59.5
unnamed: R406.2, R407.1, U$19.3
unnamed: R409.2, R410.1, U$36.3
unnamed: R412.2, U$11.LED_YG_G-
unnamed: C532.+, JP8.2
unnamed: R493.1, R494.2, U73.30
unnamed: R495.2, R496.1, U73.29
unnamed: R497.1, U73.31
unnamed: C566.2, R498.2, R499.1, Y6.1
unnamed: R499.2, U73.11
unnamed: R500.2, U73.12
unnamed: C567.2, R498.1, R500.1, Y6.3
unnamed: R501.1, U73.1
unnamed: R502.1, U73.3
unnamed: R503.1, U73.5
unnamed: R504.1, U73.7
unnamed: R505.1, U73.8
unnamed: R506.1, U73.17
unnamed: R507.1, U73.18
unnamed: R508.1, U73.20
unnamed: Q14.1, R525.2
unnamed: Q15.1, R524.1
unnamed: D20.P$2, Q15.3
unnamed: D19.P$2, Q14.3
unnamed: D19.P$1, D20.P$1, R526.1
unnamed: Q16.1, R527.2
unnamed: D21.P$2, Q16.3
unnamed: D21.P$1, R528.1
unnamed: Q17.1, R530.2
unnamed: D22.P$2, Q17.3
unnamed: D22.P$1, R531.1
unnamed: R533.1, U75.2
unnamed: R534.2, U75.1
unnamed: J26.B3, R573.2
unnamed: R535.1, U75.10
unnamed: R580.2, U$38.C3
unnamed: C604.2, U83.7
unnamed: R600.1, R601.2, U83.2
unnamed: C605.2, U83.5
unnamed: C602.1, U83.16
unnamed: R602.2, U83.3
unnamed: D30.P$1, R607.2
unnamed: C575.1, R536.1, R537.2, U76.3
unnamed: C577.1, U77.5
unnamed: R543.1, U78.4
unnamed: R540.1, R541.2, U77.3
unnamed: R544.1, R545.2, U79.4
unnamed: R546.2, R547.1, U79.3
unnamed: R548.2, U79.1
unnamed: D24.A, F1.2, R549.2, SMCJ64CA.A
unnamed: C626.1, R612.2, U$11.SHIELD@1, U$11.SHIELD@2
unnamed: D26.P$2, R549.1
unnamed: C607.2, R606.1
unnamed: C580.2, Q20.1, U79.10
unnamed: R550.2, U79.9
unnamed: D28.C, Q21.1, R554.1
unnamed: C581.1, U79.7
unnamed: D27.P$2, R552.1
unnamed: D29.P$1, R555.2
unnamed: R553.2, R554.2, U79.8
unnamed: D29.P$2, Q21.3
unnamed: Q19.1, U80.5
unnamed: R556.2, S5.P, U80.2
unnamed: R560.1, U1.AF10
unnamed: R561.1, U1.AF9
unnamed: R562.1, U1.AE9
unnamed: R563.1, U1.AE8
unnamed: R413.2, U$17.LED_G-
unnamed: R414.2, U$17.LED_YG_G-
unnamed: R415.2, U$12.LED_G-
unnamed: R416.2, U$12.LED_YG_G-
unnamed: R581.2, U$38.B2
unnamed: R557.1, U1.AC14
unnamed: R558.1, U1.AC9
unnamed: D31.P$1, R608.2
unnamed: C624.1, R610.2, U$17.SHIELD@1, U$17.SHIELD@2
unnamed: C625.1, R611.2, U$12.SHIELD@1, U$12.SHIELD@2
OLDI_A0_N: J26.C3, R572.1, U1.J28
OLDI_A0_P: J26.C4, R572.2, U1.K28
OLDI_A1_N: J26.D6, R571.1, U1.L27
OLDI_A1_P: J26.D5, R571.2, U1.K27
OLDI_A2_N: J26.D10, R570.1, U1.K24
OLDI_A2_P: J26.D9, R570.2, U1.J24
OLDI_A3_N: J26.D1, R569.1, U1.J26
OLDI_A3_P: J26.D2, R569.2, U1.K26
OLDI_CLK_N: J26.C8, R568.1, U1.L25
OLDI_CLK_P: J26.C7, R568.2, U1.K25
OSC0: C49.1, U18.88, Y2.3
OSC1: C50.1, U18.89, Y2.1
OSC1_XI: R308.2, U1.C22
OSC1_XO: R309.2, U1.E22
OSPI_CLK: R581.1, R583.2, U1.V1
OSPI_CS: R582.2, U1.R4, U$38.C2
OSPI_D0: R591.2, U1.U4, U$38.D3
OSPI_D1: R590.2, U1.U5, U$38.D2
OSPI_D2: R589.2, U1.T2, U$38.C4
OSPI_D3: R588.2, U1.T3, U$38.D4
OSPI_D4: R587.2, U1.T4, U$38.D5
OSPI_D5: R586.2, U1.T5, U$38.E3
OSPI_D6: R585.2, U1.R2, U$38.E2
OSPI_D7: R584.2, U1.R3, U$38.E1
OSPI_DQS: R580.1, U1.U2
PERIF_TCK: R104.2, U32.3
PMIC_POWER_EN0: TP6.TP, U1.Y5
PMIC_POWER_EN1: TP7.TP, U1.AA5
PORZ_OUT: R64.1, R327.1, U1.C19, U17.2, U23.2, U33.2, U52.2, U57.2, U58.2, U81.2, U82.2
PRG0_UART0_CTS: J28.C29, U1.V26
PRG0_UART0_RTS: J28.C30, U1.U25
PRG0_UART0_RX: J28.C28, U1.Y28
PRG0_UART0_TX: J28.C27, U1.AA28
PRG1_UART0_CTS: J28.C22, U1.AF26
PRG1_UART0_RTS: J28.C23, U1.AH25
PRG1_UART0_RX: J28.C24, U1.AF25
PRG1_UART0_TX: J28.C25, U1.AF24
PRG2_ETH1_D0_N: U54.2, U$11.MD1-
PRG2_ETH1_D0_P: U54.1, U$11.MD1+
PRG2_ETH1_D1_N: U54.5, U$11.MD2-
PRG2_ETH1_D1_P: U54.4, U$11.MD2+
PRG2_ETH1_D2_N: U54.8, U$11.MD3-
PRG2_ETH1_D2_P: U54.7, U$11.MD3+
PRG2_ETH1_D3_N: U54.11, U$11.MD4-
PRG2_ETH1_D3_P: U54.10, U$11.MD4+
PRG2_ETH1_GPIO0: R355.2, R433.1, R439.2, U54.39
PRG2_ETH1_GPIO1: R445.2, R446.1, U54.40
PRG2_ETH1_LED1: Q3.3, R151.1
PRG2_ETH1_LED2: Q2.3, R356.1, U$11.LED_YG_G+
PRG2_ETH1_LED3: Q1.3, R357.1, R412.1
PRG2_ETH1_LED_1000: R354.2, R435.1, R441.2, U54.45
PRG2_ETH1_LED_ACTIVITY: R353.2, R434.1, R440.2, U54.46
PRG2_ETH2_D0_N: U55.2, U$12.MD1-
PRG2_ETH2_D0_P: U55.1, U$12.MD1+
PRG2_ETH2_D1_N: U55.5, U$12.MD2-
PRG2_ETH2_D1_P: U55.4, U$12.MD2+
PRG2_ETH2_D2_N: U55.8, U$12.MD3-
PRG2_ETH2_D2_P: U55.7, U$12.MD3+
PRG2_ETH2_D3_N: U55.11, U$12.MD4-
PRG2_ETH2_D3_P: U55.10, U$12.MD4+
PRG2_ETH2_GPIO0: R369.2, R447.1, R453.2, U55.39
PRG2_ETH2_GPIO1: R459.2, R460.1, U55.40
PRG2_ETH2_LED1: Q13.3, R415.1
PRG2_ETH2_LED2: Q12.3, R370.1, U$12.LED_YG_G+
PRG2_ETH2_LED3: Q4.3, R371.1, R416.1
PRG2_ETH2_LED_1000: R368.2, R449.1, R455.2, U55.45
PRG2_ETH2_LED_ACTIVITY: R367.2, R448.1, R454.2, U55.46
PRG2_ETH_LED0: R527.1, R529.2, U56.7
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
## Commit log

2020-09-12 Add initial files
2020-09-12 Update gitignore
2020-10-09 Update README.md
    Fix formatting
2020-10-09 Update README.md
    Fixed it again
2020-10-09 Update README.md
    omg can this thing work?
2020-10-09 Update README.md
    screw this

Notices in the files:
parts and their libraries:
microbuilder: This work is placed in the public domain, and may be freely used for commercial and non-commercial work with the following conditions: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
SparkFun-Retired: Licensing: Creative Commons ShareAlike 4.0 International - https://creativecommons.org/licenses/by-sa/4.0
